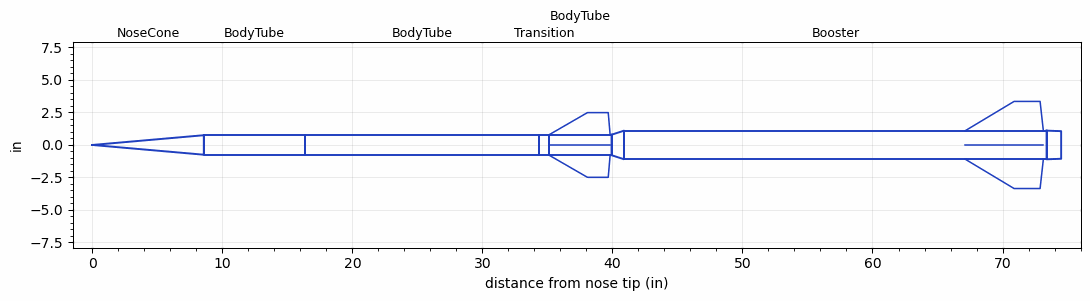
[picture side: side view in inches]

<RASAeroDocument>
 <FileVersion>2</FileVersion>
 <RocketDesign>
  <NoseCone>
   <Length>8.57</Length>
   <Diameter>1.5</Diameter>
   <Shape>Conical</Shape>
   <BluntRadius>0.065</BluntRadius>
   <Location>0</Location>
  </NoseCone>
  <BodyTube>
   <Length>7.75</Length>
   <Diameter>1.5</Diameter>
   <Location>8.57</Location>
  </BodyTube>
  <BodyTube>
   <Length>18.03</Length>
   <Diameter>1.5</Diameter>
   <Location>16.32</Location>
  </BodyTube>
  <Transition>
   <Length>0.75</Length>
   <Diameter>1.575</Diameter>
   <Location>34.35</Location>
   <RearDiameter>1.575</RearDiameter>
  </Transition>
  <BodyTube>
   <Length>4.83</Length>
   <Diameter>1.575</Diameter>
   <Location>35.1</Location>
   <Fin>
    <Count>4</Count>
    <Chord>4.69</Chord>
    <Span>1.7</Span>
    <SweepDistance>2.944</SweepDistance>
    <TipChord>1.6</TipChord>
    <Thickness>0.1</Thickness>
    <LERadius>0.024</LERadius>
    <Location>4.8</Location>
    <AirfoilSection>Double Wedge</AirfoilSection>
    <FX1>0.8</FX1>
    <FX3>0.25</FX3>
   </Fin>
  </BodyTube>
  <Booster>
   <Length>32.5</Length>
   <Diameter>2.2</Diameter>
   <InsideDiameter>1.575</InsideDiameter>
   <Location>39.93</Location>
   <ShoulderLength>0.96</ShoulderLength>
   <BoattailLength>1.12</BoattailLength>
   <BoattailRearDiameter>2.125</BoattailRearDiameter>
   <Fin>
    <Count>4</Count>
    <Chord>6</Chord>
    <Span>2.25</Span>
    <SweepDistance>3.75</SweepDistance>
    <TipChord>2</TipChord>
    <Thickness>0.118</Thickness>
    <LERadius>0.02</LERadius>
    <Location>6.25</Location>
    <AirfoilSection>Hexagonal</AirfoilSection>
    <FX1>0.75</FX1>
    <FX3>0.75</FX3>
   </Fin>
  </Booster>
  <Surface>Rough Camouflage Paint</Surface>
  <ModifiedBarrowman>True</ModifiedBarrowman>
  <Turbulence>True</Turbulence>
  <UseBooster1>False</UseBooster1>
  <UseBooster2>False</UseBooster2>
 </RocketDesign>
 <LaunchSite>
  <Altitude>4000</Altitude>
  <Pressure>29.9</Pressure>
  <RodAngle>5</RodAngle>
  <RodLength>10</RodLength>
  <Temperature>90</Temperature>
  <WindSpeed>10</WindSpeed>
 </LaunchSite>
 <Recovery>
  <Altitude1>1000</Altitude1>
  <Altitude2>1000</Altitude2>
  <DeviceType1>None</DeviceType1>
  <DeviceType2>None</DeviceType2>
  <Event1>False</Event1>
  <Event2>False</Event2>
  <Size1>1</Size1>
  <Size2>1</Size2>
  <EventType1>None</EventType1>
  <EventType2>None</EventType2>
  <CD1>1.33</CD1>
  <CD2>1.33</CD2>
 </Recovery>
 <SimulationList>
  <Simulation>
   <SustainerEngine>J495AP(NC)  (Polaris)</SustainerEngine>
   <SustainerLaunchWt>3.6</SustainerLaunchWt>
   <SustainerNozzleDiameter>1.325</SustainerNozzleDiameter>
   <SustainerCG>21.86</SustainerCG>
   <SustainerIgnitionDelay>5</SustainerIgnitionDelay>
   <Booster1Engine>L1000  (AT)</Booster1Engine>
   <Booster1LaunchWt>9.6</Booster1LaunchWt>
   <Booster1SeparationDelay>0</Booster1SeparationDelay>
   <Booster1IgnitionDelay>0</Booster1IgnitionDelay>
   <Booster1CG>45.4</Booster1CG>
   <Booster1NozzleDiameter>1.25</Booster1NozzleDiameter>
   <IncludeBooster1>True</IncludeBooster1>
   <Booster2Delay>0</Booster2Delay>
   <IncludeBooster2>False</IncludeBooster2>
   <TimetoApogee>48.12843</TimetoApogee>
   <MaxAltitude>48341.38</MaxAltitude>
   <MaxVelocity>3504.394</MaxVelocity>
   <OptimumWt>3.7125</OptimumWt>
   <OptimumMaxAlt>3.7125</OptimumMaxAlt>
  </Simulation>
 </SimulationList>
</RASAeroDocument>
